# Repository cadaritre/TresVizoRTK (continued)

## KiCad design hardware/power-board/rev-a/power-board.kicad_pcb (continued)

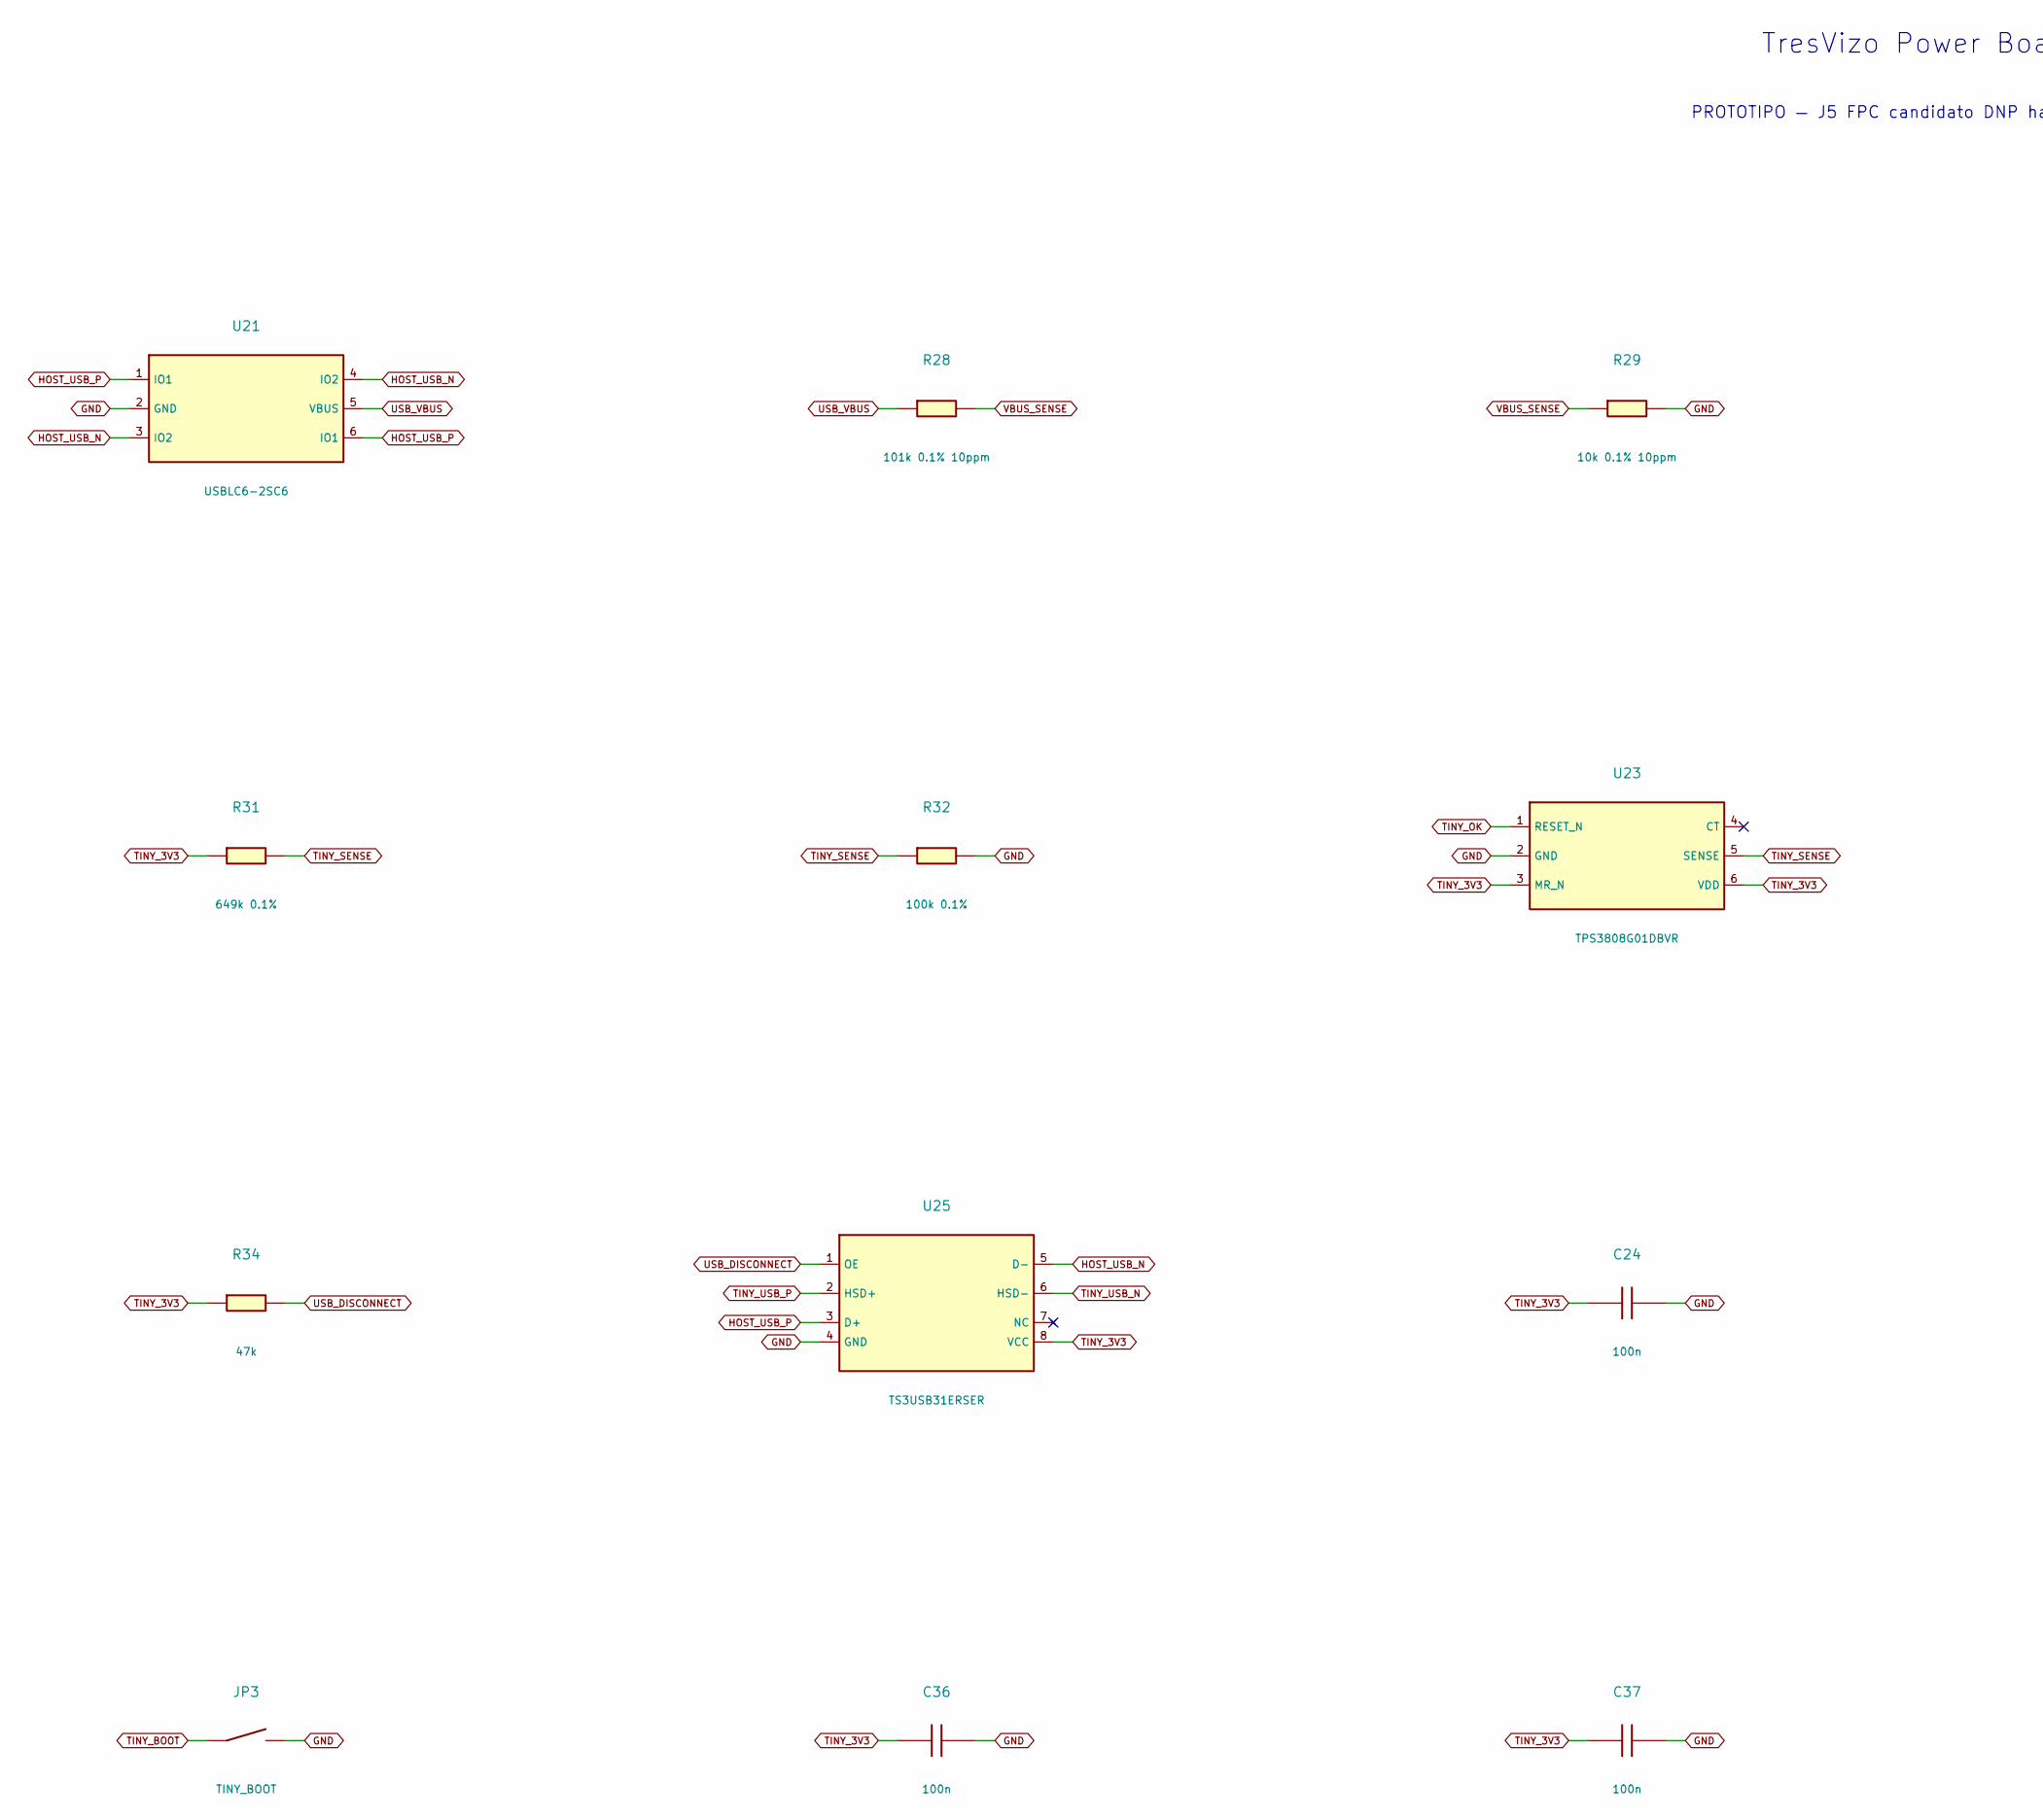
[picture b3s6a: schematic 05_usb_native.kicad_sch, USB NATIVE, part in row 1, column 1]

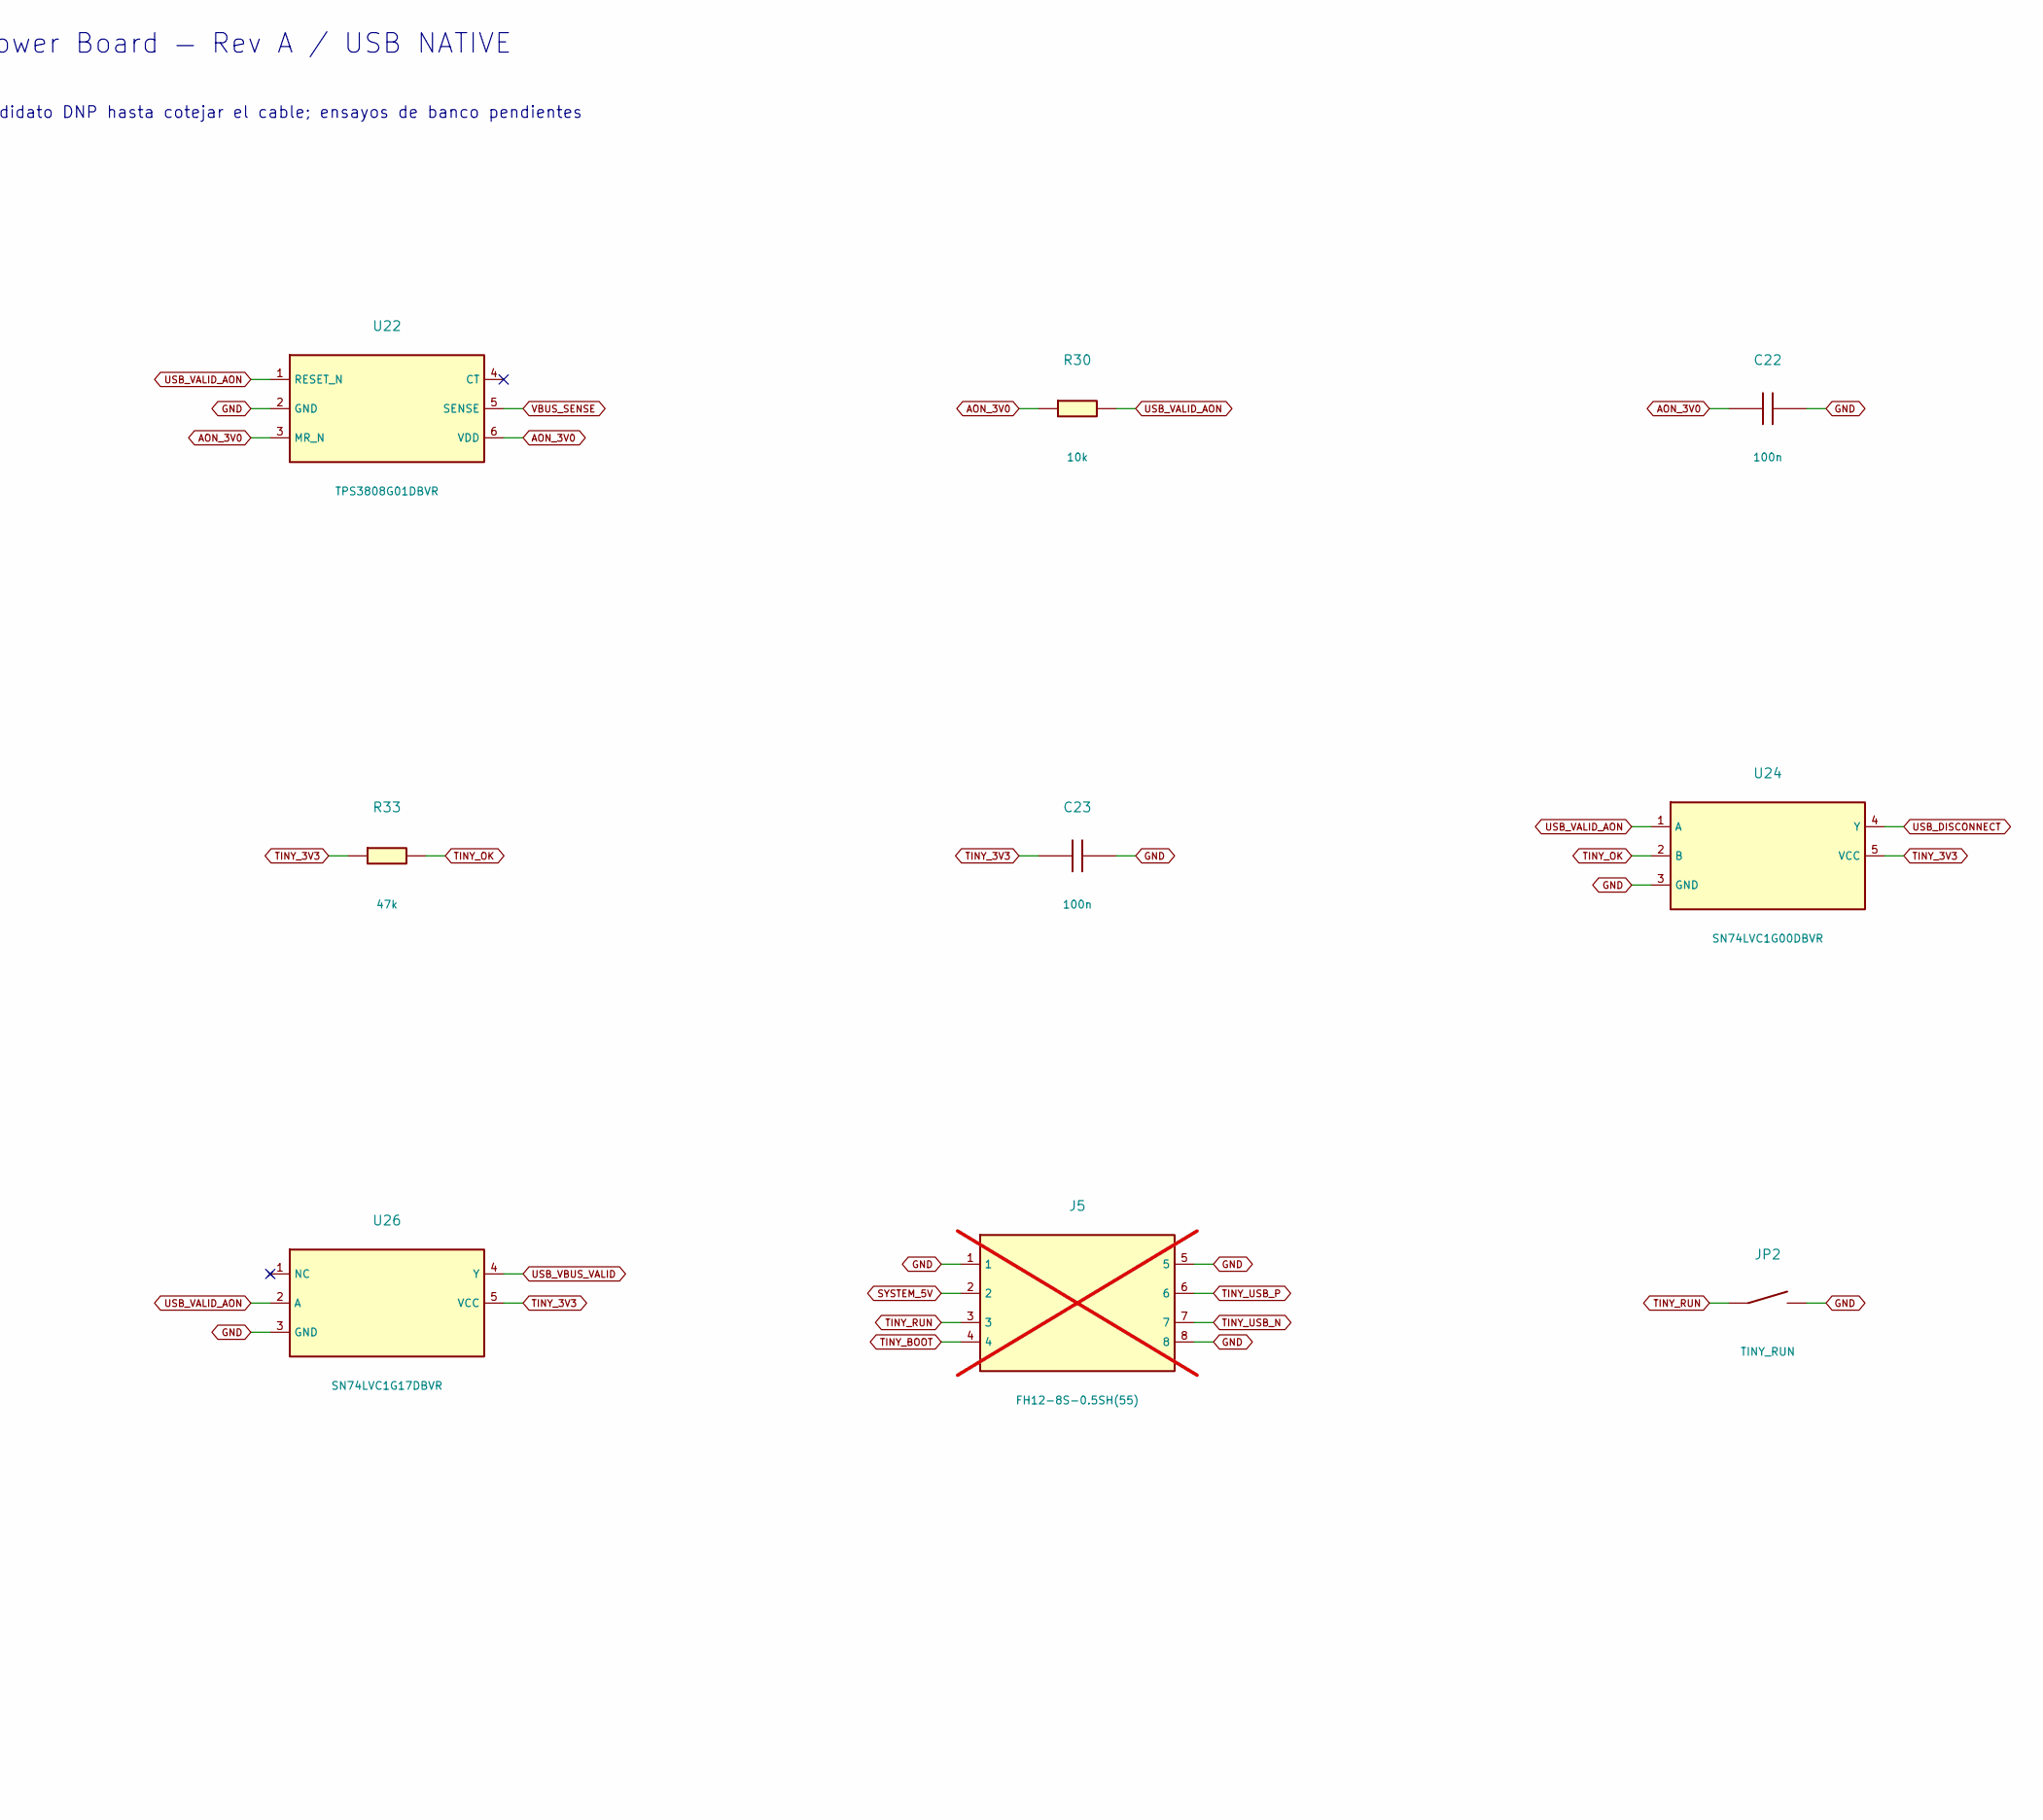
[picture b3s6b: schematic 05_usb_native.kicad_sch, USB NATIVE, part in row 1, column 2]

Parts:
C22, C23, C24, C36, C37: 100n; C_0603_1608Metric; MPN CC0603KRX7R9BB104
J5: FH12-8S-0.5SH(55); Hirose_FH12-8S-0.5SH_1x08-1MP_P0.50mm_Horizontal; MPN FH12-8S-0.5SH(55); not fitted
JP2: TINY_RUN; SolderJumper-2_P1.3mm_Open_Pad1.0x1.5mm; MPN OPEN
JP3: TINY_BOOT; SolderJumper-2_P1.3mm_Open_Pad1.0x1.5mm; MPN OPEN
R28: 101k 0.1% 10ppm; R_0603_1608Metric; MPN RT0603BRB07101KL
R29: 10k 0.1% 10ppm; R_0603_1608Metric; MPN RT0603BRB0710KL
R30: 10k; R_0603_1608Metric; MPN RC0603FR-0710KL
R31: 649k 0.1%; R_0603_1608Metric; MPN RT0603BRD07649KL
R32: 100k 0.1%; R_0603_1608Metric; MPN RT0603BRD07100KL
R33, R34: 47k; R_0603_1608Metric; MPN RC0603FR-0747KL
U21: USBLC6-2SC6; SOT-23-6; MPN USBLC6-2SC6
U22, U23: TPS3808G01DBVR; SOT-23-6; MPN TPS3808G01DBVR
U24: SN74LVC1G00DBVR; SOT-23-5; MPN SN74LVC1G00DBVR
U25: TS3USB31ERSER; Texas_UQFN-8_1.5x1.5mm_P0.5mm; MPN TS3USB31ERSER
U26: SN74LVC1G17DBVR; SOT-23-5; MPN SN74LVC1G17DBVR

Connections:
AON_3V0: C22.1, R30.1, U22.3 (MR_N), U22.6 (VDD); also elsewhere on the board
GND: C22.2, C23.2, C24.2, C36.2, C37.2, J5.1, J5.5, J5.8, JP2.2, JP3.2, R29.2, R32.2, U21.2 (GND), U22.2 (GND), U23.2 (GND), U24.3 (GND), U25.4 (GND), U26.3 (GND); also elsewhere on the board
HOST_USB_N: U21.3 (IO2), U21.4 (IO2), U25.5 (D-); also elsewhere on the board
HOST_USB_P: U21.1 (IO1), U21.6 (IO1), U25.3 (D+); also elsewhere on the board
SYSTEM_5V: J5.2; also elsewhere on the board
TINY_3V3: C23.1, C24.1, C36.1, C37.1, R31.1, R33.1, R34.1, U23.3 (MR_N), U23.6 (VDD), U24.5 (VCC), U25.8 (VCC), U26.5 (VCC); also elsewhere on the board
TINY_BOOT: J5.4, JP3.1
TINY_OK: R33.2, U23.1 (RESET_N), U24.2 (B); also elsewhere on the board
TINY_RUN: J5.3, JP2.1
TINY_SENSE: R31.2, R32.1, U23.5 (SENSE)
TINY_USB_N: J5.7, U25.6 (HSD-); also elsewhere on the board
TINY_USB_P: J5.6, U25.2 (HSD+); also elsewhere on the board
USB_DISCONNECT: R34.2, U24.4 (Y), U25.1 (OE)
USB_VALID_AON: R30.2, U22.1 (RESET_N), U24.1 (A), U26.2 (A); also elsewhere on the board
USB_VBUS: R28.1, U21.5 (VBUS); also elsewhere on the board
USB_VBUS_VALID: U26.4 (Y); also elsewhere on the board
VBUS_SENSE: R28.2, R29.1, U22.5 (SENSE)

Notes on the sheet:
TresVizo Power Board — Rev A / USB NATIVE
PROTOTIPO — J5 FPC candidato DNP hasta cotejar el cable; ensayos de banco pendientes

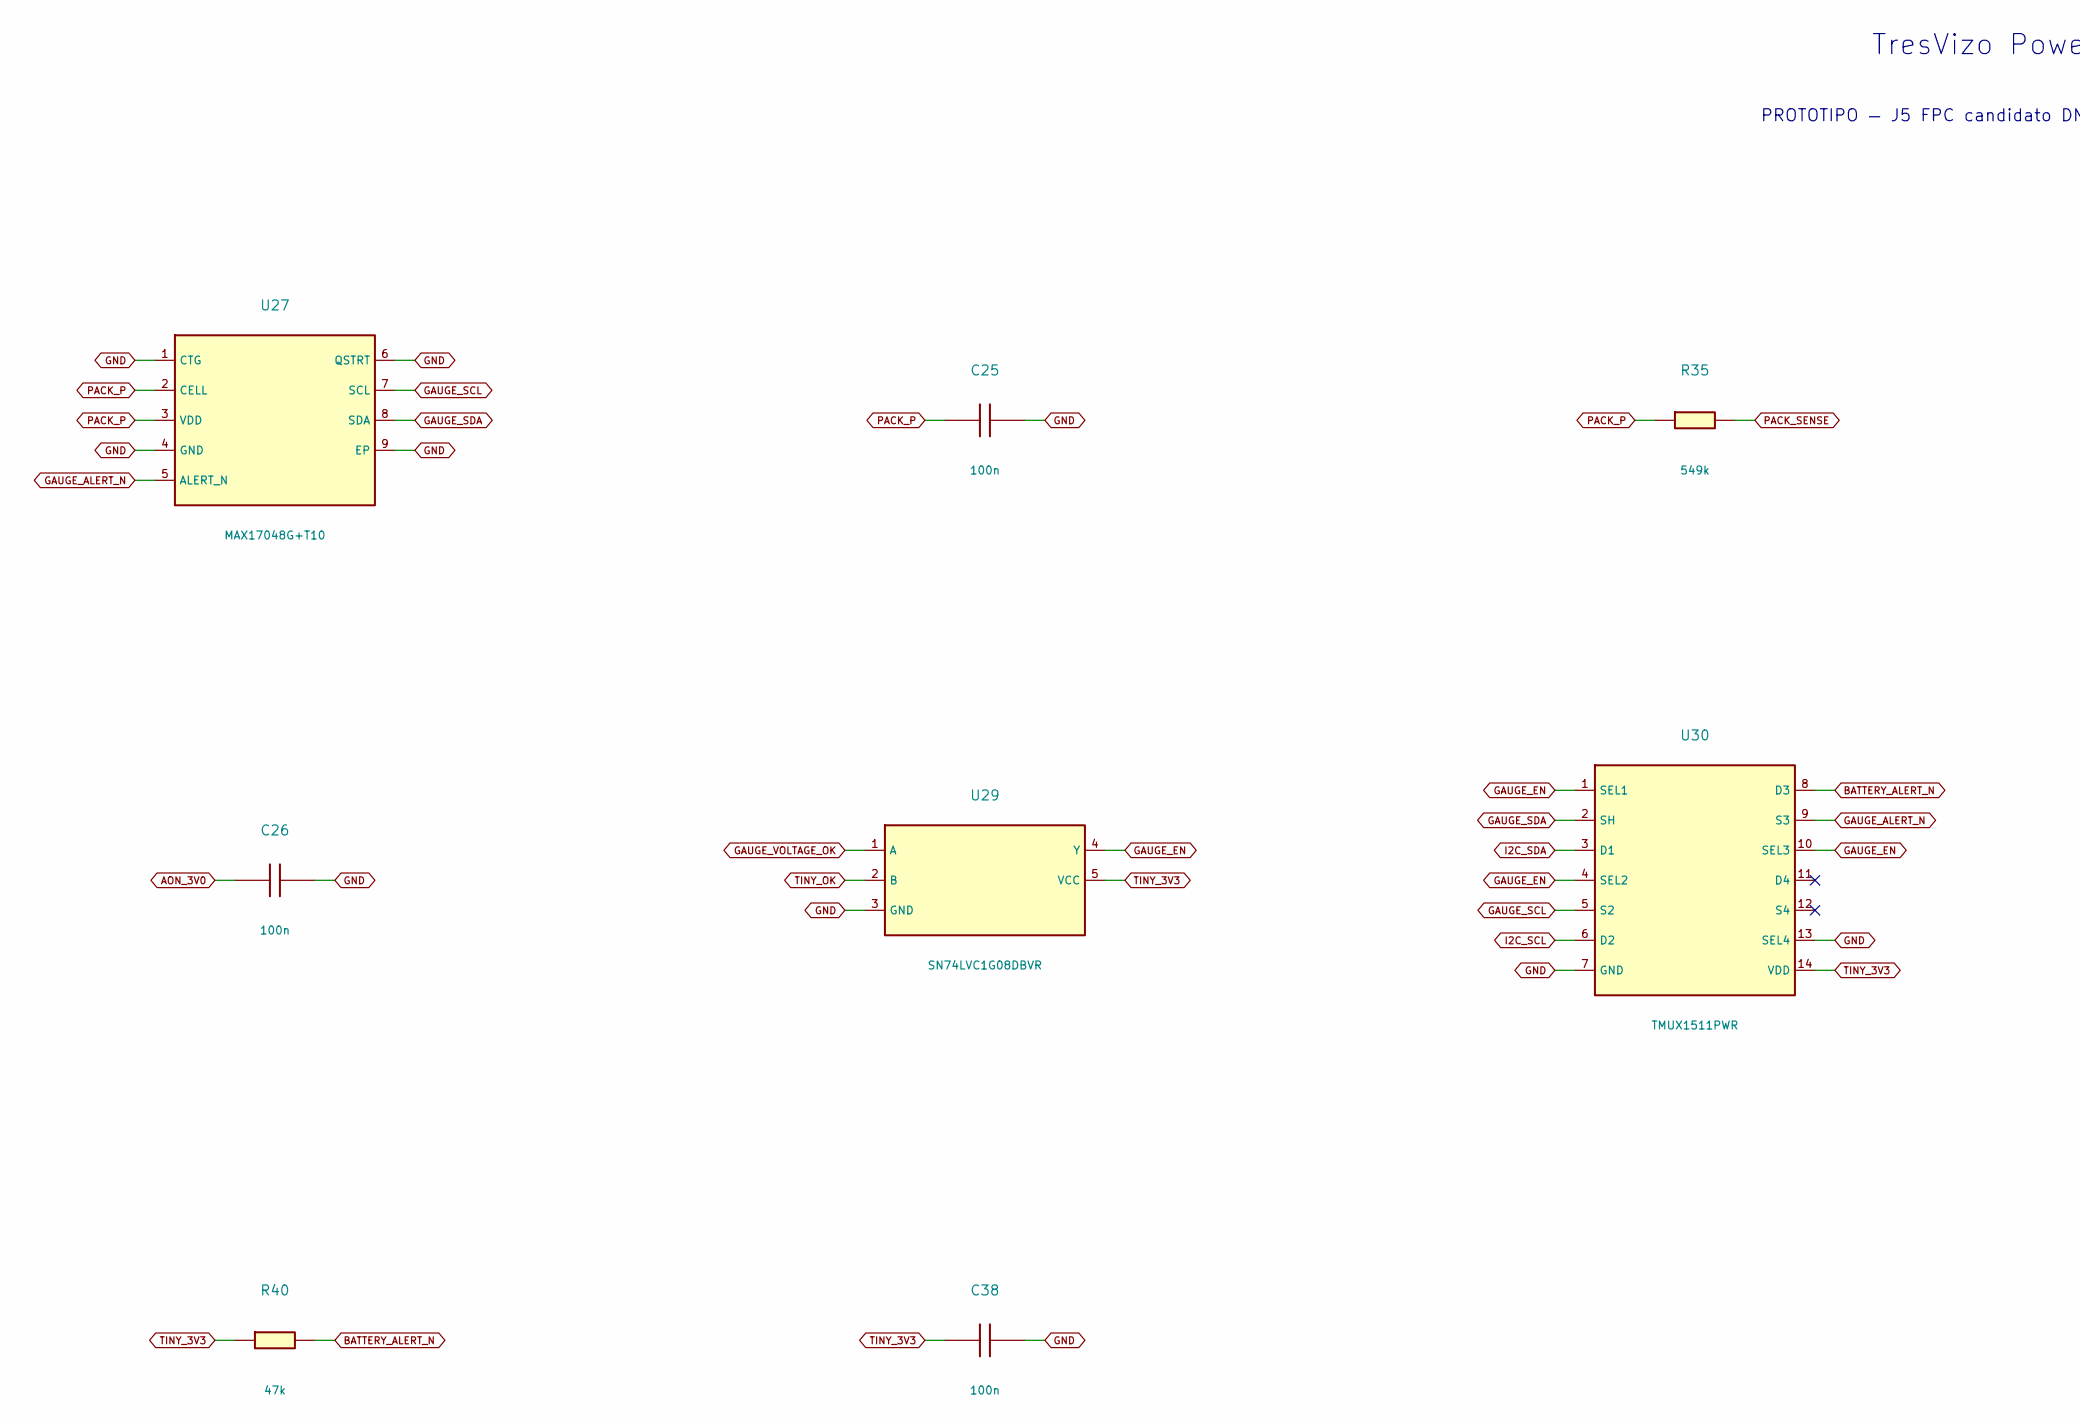
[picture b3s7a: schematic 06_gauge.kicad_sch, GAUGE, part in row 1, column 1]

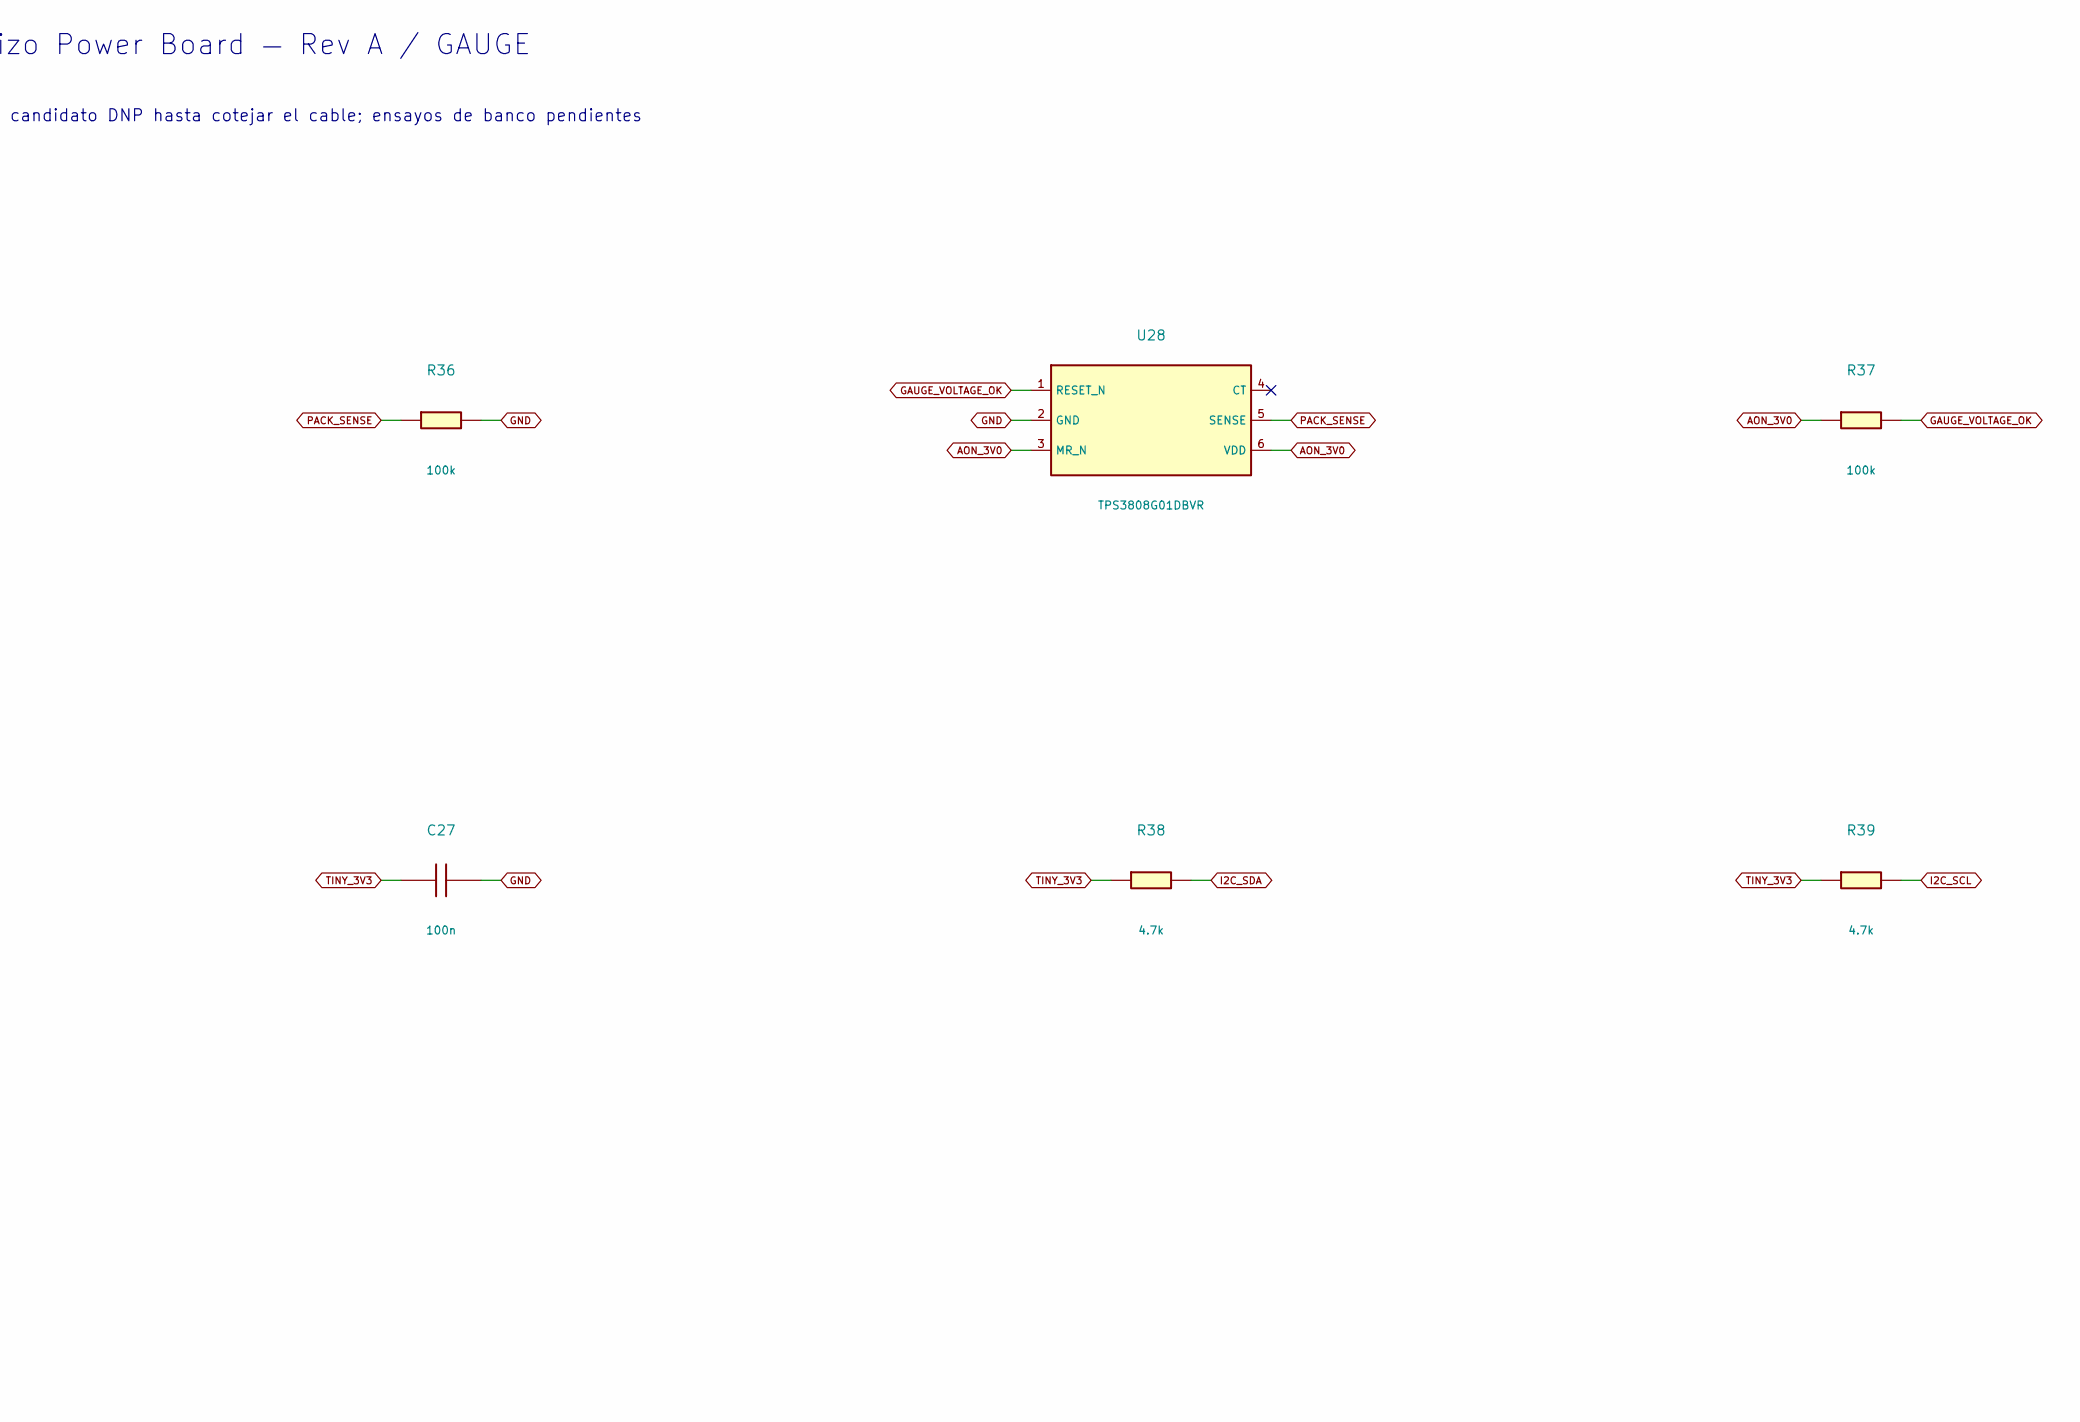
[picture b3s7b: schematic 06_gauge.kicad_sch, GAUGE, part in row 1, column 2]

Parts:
C25, C26, C27, C38: 100n; C_0603_1608Metric; MPN CC0603KRX7R9BB104
R35: 549k; R_0603_1608Metric; MPN RC0603FR-07549KL
R36, R37: 100k; R_0603_1608Metric; MPN RC0603FR-07100KL
R38, R39: 4.7k; R_0603_1608Metric; MPN RC0603FR-074K7L
R40: 47k; R_0603_1608Metric; MPN RC0603FR-0747KL
U27: MAX17048G+T10; TDFN-8-1EP_2x2mm_P0.5mm_EP0.8x1.2mm; MPN MAX17048G+T10
U28: TPS3808G01DBVR; SOT-23-6; MPN TPS3808G01DBVR
U29: SN74LVC1G08DBVR; SOT-23-5; MPN SN74LVC1G08DBVR
U30: TMUX1511PWR; TSSOP-14_4.4x5mm_P0.65mm; MPN TMUX1511PWR

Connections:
AON_3V0: C26.1, R37.1, U28.3 (MR_N), U28.6 (VDD); also elsewhere on the board
BATTERY_ALERT_N: R40.2, U30.8 (D3); also elsewhere on the board
GAUGE_ALERT_N: U27.5 (ALERT_N), U30.9 (S3)
GAUGE_EN: U29.4 (Y), U30.1 (SEL1), U30.4 (SEL2), U30.10 (SEL3)
GAUGE_SCL: U27.7 (SCL), U30.5 (S2)
GAUGE_SDA: U27.8 (SDA), U30.2 (SH)
GAUGE_VOLTAGE_OK: R37.2, U28.1 (RESET_N), U29.1 (A)
GND: C25.2, C26.2, C27.2, C38.2, R36.2, U27.1 (CTG), U27.4 (GND), U27.6 (QSTRT), U27.9 (EP), U28.2 (GND), U29.3 (GND), U30.7 (GND), U30.13 (SEL4); also elsewhere on the board
I2C_SCL: R39.2, U30.6 (D2); also elsewhere on the board
I2C_SDA: R38.2, U30.3 (D1); also elsewhere on the board
PACK_P: C25.1, R35.1, U27.2 (CELL), U27.3 (VDD); also elsewhere on the board
PACK_SENSE: R35.2, R36.1, U28.5 (SENSE)
TINY_3V3: C27.1, C38.1, R38.1, R39.1, R40.1, U29.5 (VCC), U30.14 (VDD); also elsewhere on the board
TINY_OK: U29.2 (B); also elsewhere on the board

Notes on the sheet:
TresVizo Power Board — Rev A / GAUGE
PROTOTIPO — J5 FPC candidato DNP hasta cotejar el cable; ensayos de banco pendientes
